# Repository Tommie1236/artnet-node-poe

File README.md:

# Art-Net Node PoE — v2

A compact, fully SMD Art-Net node with Power over Ethernet (PoE) support and two bidirectional DMX512 ports.

---

## Table of Contents

- [Overview](#overview)
- [Features](#features)
- [What is Art-Net?](#what-is-art-net)
- [What is DMX512?](#what-is-dmx512)
- [Hardware](#hardware)
  - [v1 vs v2](#v1-vs-v2)
  - [Board Design](#board-design)
  - [Power](#power)
  - [DMX Ports](#dmx-ports)
- [Getting Started](#getting-started)
  - [Powering the Node](#powering-the-node)
  - [Connecting DMX Devices](#connecting-dmx-devices)
  - [Network Configuration](#network-configuration)
- [Usage](#usage)
- [Planned Features](#planned-features)
- [Contributing](#contributing)
- [License](#license)

---

## Overview

This project is the second generation of a DIY Art-Net node — a device that bridges an Ethernet network running the [Art-Net protocol](https://art-net.org.uk/) to standard DMX512 lighting fixtures and controllers.

The v1 node ([pico-art-net-node](https://github.com/Tommie1236/pico-art-net-node)) was built around a **Raspberry Pi Pico** with separate breakout modules: a WIZnet W5500 Ethernet module, an isolated RS-485 transceiver board, and an SSD1306 OLED display. While that approach worked well for prototyping, it produced a larger assembly with many inter-board connections.

The v2 design integrates everything onto a single PCB using **fully surface-mount components** — no separate Pico module, no separate W5500 module. The result is a much more compact and reliable board. Three power inputs are supported (USB, DC jack, and PoE) with automatic hardware priority so PoE is only used when nothing else is connected. v2 also expands from one DMX port to **two independent bidirectional DMX512 ports** with XLR3 connectors, and uses an EtherCon-compatible connector for a robust Ethernet connection.

---

## Features

| Feature | v1 ([pico-art-net-node](https://github.com/Tommie1236/pico-art-net-node)) | v2 (this project) |
|---|---|---|
| PCB design | THT breakout modules (Pico, W5500, RS-485 board) | Fully SMD, single PCB |
| Microcontroller | Raspberry Pi Pico (RP2040 module) | Integrated SMD MCU |
| Ethernet | WIZnet W5500 breakout module | Integrated SMD Ethernet |
| DMX ports | 1 (output) | 2 (Port A & Port B) |
| DMX direction | Output only | Input **and** Output per port |
| Display | SSD1306 OLED | — |
| Power source | External supply only | USB, DC jack, or PoE (priority: USB > DC > PoE) |
| RDM support | No | Planned |

- **Fully SMD layout** — no bulky THT breakout modules; compact, clean, and reliable.
- **Three power inputs with automatic priority** — USB (highest), DC barrel jack, or PoE (lowest). The node automatically uses the highest-priority source available, so plugging in USB or DC disables PoE, saving switch capacity and reducing cable losses.
- **EtherCon connector** — the RJ45 Ethernet port uses an EtherCon-compatible connector/housing for a robust, locking connection in live environments.
- **Two DMX512 ports** — both Port A and Port B support DMX **output** (Art-Net → DMX) and DMX **input** (DMX → Art-Net).
- **Standard Art-Net protocol** — compatible with any Art-Net controller or software (e.g., MA Lighting, QLC+, MadMapper, sACN bridges, etc.).
- **Future RDM support** — the hardware is designed with RDM in mind for a future firmware update.

---

## What is Art-Net?

[Art-Net](https://art-net.org.uk/) is a royalty-free protocol developed by Artistic Licence that allows DMX512 data to be transmitted over standard Ethernet (UDP/IP) networks. It is widely used in professional and hobbyist stage lighting installations to send lighting control data over long distances, through network switches, and to multiple nodes simultaneously.

An Art-Net **node** acts as the bridge between the Ethernet network and physical DMX cables, converting incoming Art-Net packets into DMX512 signals (output mode) and/or reading DMX512 signals and forwarding them as Art-Net packets to the network (input mode).

---

## What is DMX512?

DMX512 (Digital Multiplex 512) is a serial communication standard used to control stage lighting, dimmers, LEDs, fog machines, and many other effects devices. A single DMX universe carries up to 512 channels of 8-bit data at a refresh rate typically around 44 Hz. Devices on the DMX bus are daisy-chained through XLR connectors — 3-pin (XLR3) or 5-pin (XLR5); both carry the same signal on pins 1–3.

---

## Hardware

### v1 vs v2

The original [v1 node (pico-art-net-node)](https://github.com/Tommie1236/pico-art-net-node) used a **Raspberry Pi Pico** (RP2040) as the microcontroller, paired with a WIZnet W5500 Ethernet breakout module, a separate isolated RS-485 transceiver board for DMX, and an SSD1306 OLED display for status info. All components were connected by wires and headers, which was great for iteration but produced a relatively bulky assembly.

v2 replaces this approach with a single, compact PCB:

- The RP2040 (or equivalent MCU) and Ethernet controller are placed as bare SMD components directly on the PCB, eliminating the stackable module approach.
- RS-485 transceivers and isolation are integrated on-board for both DMX ports.
- The PoE power extraction and regulation circuitry is integrated, alongside a DC barrel jack and USB port, with hardware priority logic (USB > DC > PoE).

### Board Design

- Single compact PCB with all components surface-mounted.
- Integrated Ethernet PHY and microcontroller section.
- Isolated RS-485 transceivers for each DMX port.
- PoE power extraction circuitry with USB and DC jack alternatives.
- Direction control logic for bidirectional DMX operation.
- EtherCon-compatible RJ45 connector/housing for a locking, strain-relieved Ethernet connection.

### Power

The node supports three power inputs with automatic hardware priority:

| Priority | Source | Notes |
|---|---|---|
| 1 (highest) | **USB** | Powers the node from any USB port or charger |
| 2 | **DC barrel jack** | Conventional external DC supply |
| 3 (lowest) | **Power over Ethernet (PoE)** | Power delivered over the Ethernet cable |

When a higher-priority source is connected, PoE is automatically disabled. This avoids drawing unnecessary power from the network switch and reduces losses in the UTP cable — there is no benefit in using PoE if a USB or DC supply is already plugged in.

### DMX Ports

The node provides **two independent DMX512 ports**, each with:

- A **3-pin XLR connector** (XLR3) — the most common connector used in practice for DMX512 equipment.
- An isolated RS-485 transceiver for electrical isolation from the network side.
- Software-configurable direction: **output** (receive Art-Net, drive DMX) or **input** (read DMX, send Art-Net).

Each port operates on its own Art-Net **universe**, configurable via the node's settings.

---

## Getting Started

### Powering the Node

The node automatically uses the highest-priority power source available.

**Option A — USB (highest priority):**

1. Connect a USB cable to the USB port on the node.
2. The node powers up immediately; DC and PoE are bypassed.

**Option B — DC barrel jack:**

1. Connect a suitable DC power supply to the barrel jack.
2. If no USB source is present, the node will run from DC; PoE is bypassed.

**Option C — PoE (lowest priority):**

1. Connect the node to a PoE-capable switch port or injector using a Cat5e/Cat6 Ethernet cable terminated in a standard RJ45 or EtherCon connector.
2. PoE is used only when neither USB nor DC is connected.

### Connecting DMX Devices

- **Output mode (Art-Net → DMX):** Connect Port A or Port B to the DMX input of a lighting fixture, dimmer rack, or the first device in a DMX chain.
- **Input mode (DMX → Art-Net):** Connect a DMX controller's DMX output to Port A or Port B to forward its signal onto the Art-Net network.

Use a standard **3-pin XLR (XLR3) cable** to connect DMX devices. If your fixture uses a 5-pin XLR connector, a passive XLR5 ↔ XLR3 adapter can be used (pins 1, 2, and 3 carry the DMX signal identically on both connector types).

Always **terminate** the end of a DMX chain with a 120 Ω terminator plug.

### Network Configuration

By default the node will attempt to obtain an IP address via DHCP. If no DHCP server is available it will fall back to a static IP (see firmware documentation for default address).

Configuration options (universe assignments, port directions, IP settings) are accessible via:

- A web-based configuration interface served by the node itself.
- Art-Net ArtAddress and ArtPoll packets from a compatible controller.

---

## Usage

1. Power the node via USB, DC jack, or PoE (whichever is available; highest priority wins).
2. Connect the node to your Ethernet network.
3. Open your Art-Net controller software and discover or manually add the node.
4. Assign Art-Net universes to Port A and Port B.
5. Connect your DMX fixtures or controllers to the XLR ports.
6. Start sending or receiving DMX data.

---

## Planned Features

- **RDM (Remote Device Management)** — The hardware already supports the bidirectional RS-485 communication required for RDM. A future firmware update will add full RDM support, allowing the node to discover and configure RDM-capable fixtures directly from Art-Net RDM controllers.
- Web UI improvements for easier configuration.
- sACN (E1.31) support alongside Art-Net.

---

## Contributing

Contributions are welcome! See [CONTRIBUTING.md](CONTRIBUTING.md) for guidelines.

---

## License

This project is licensed under the [MIT License](LICENSE).

Copyright © 2026 Timoo

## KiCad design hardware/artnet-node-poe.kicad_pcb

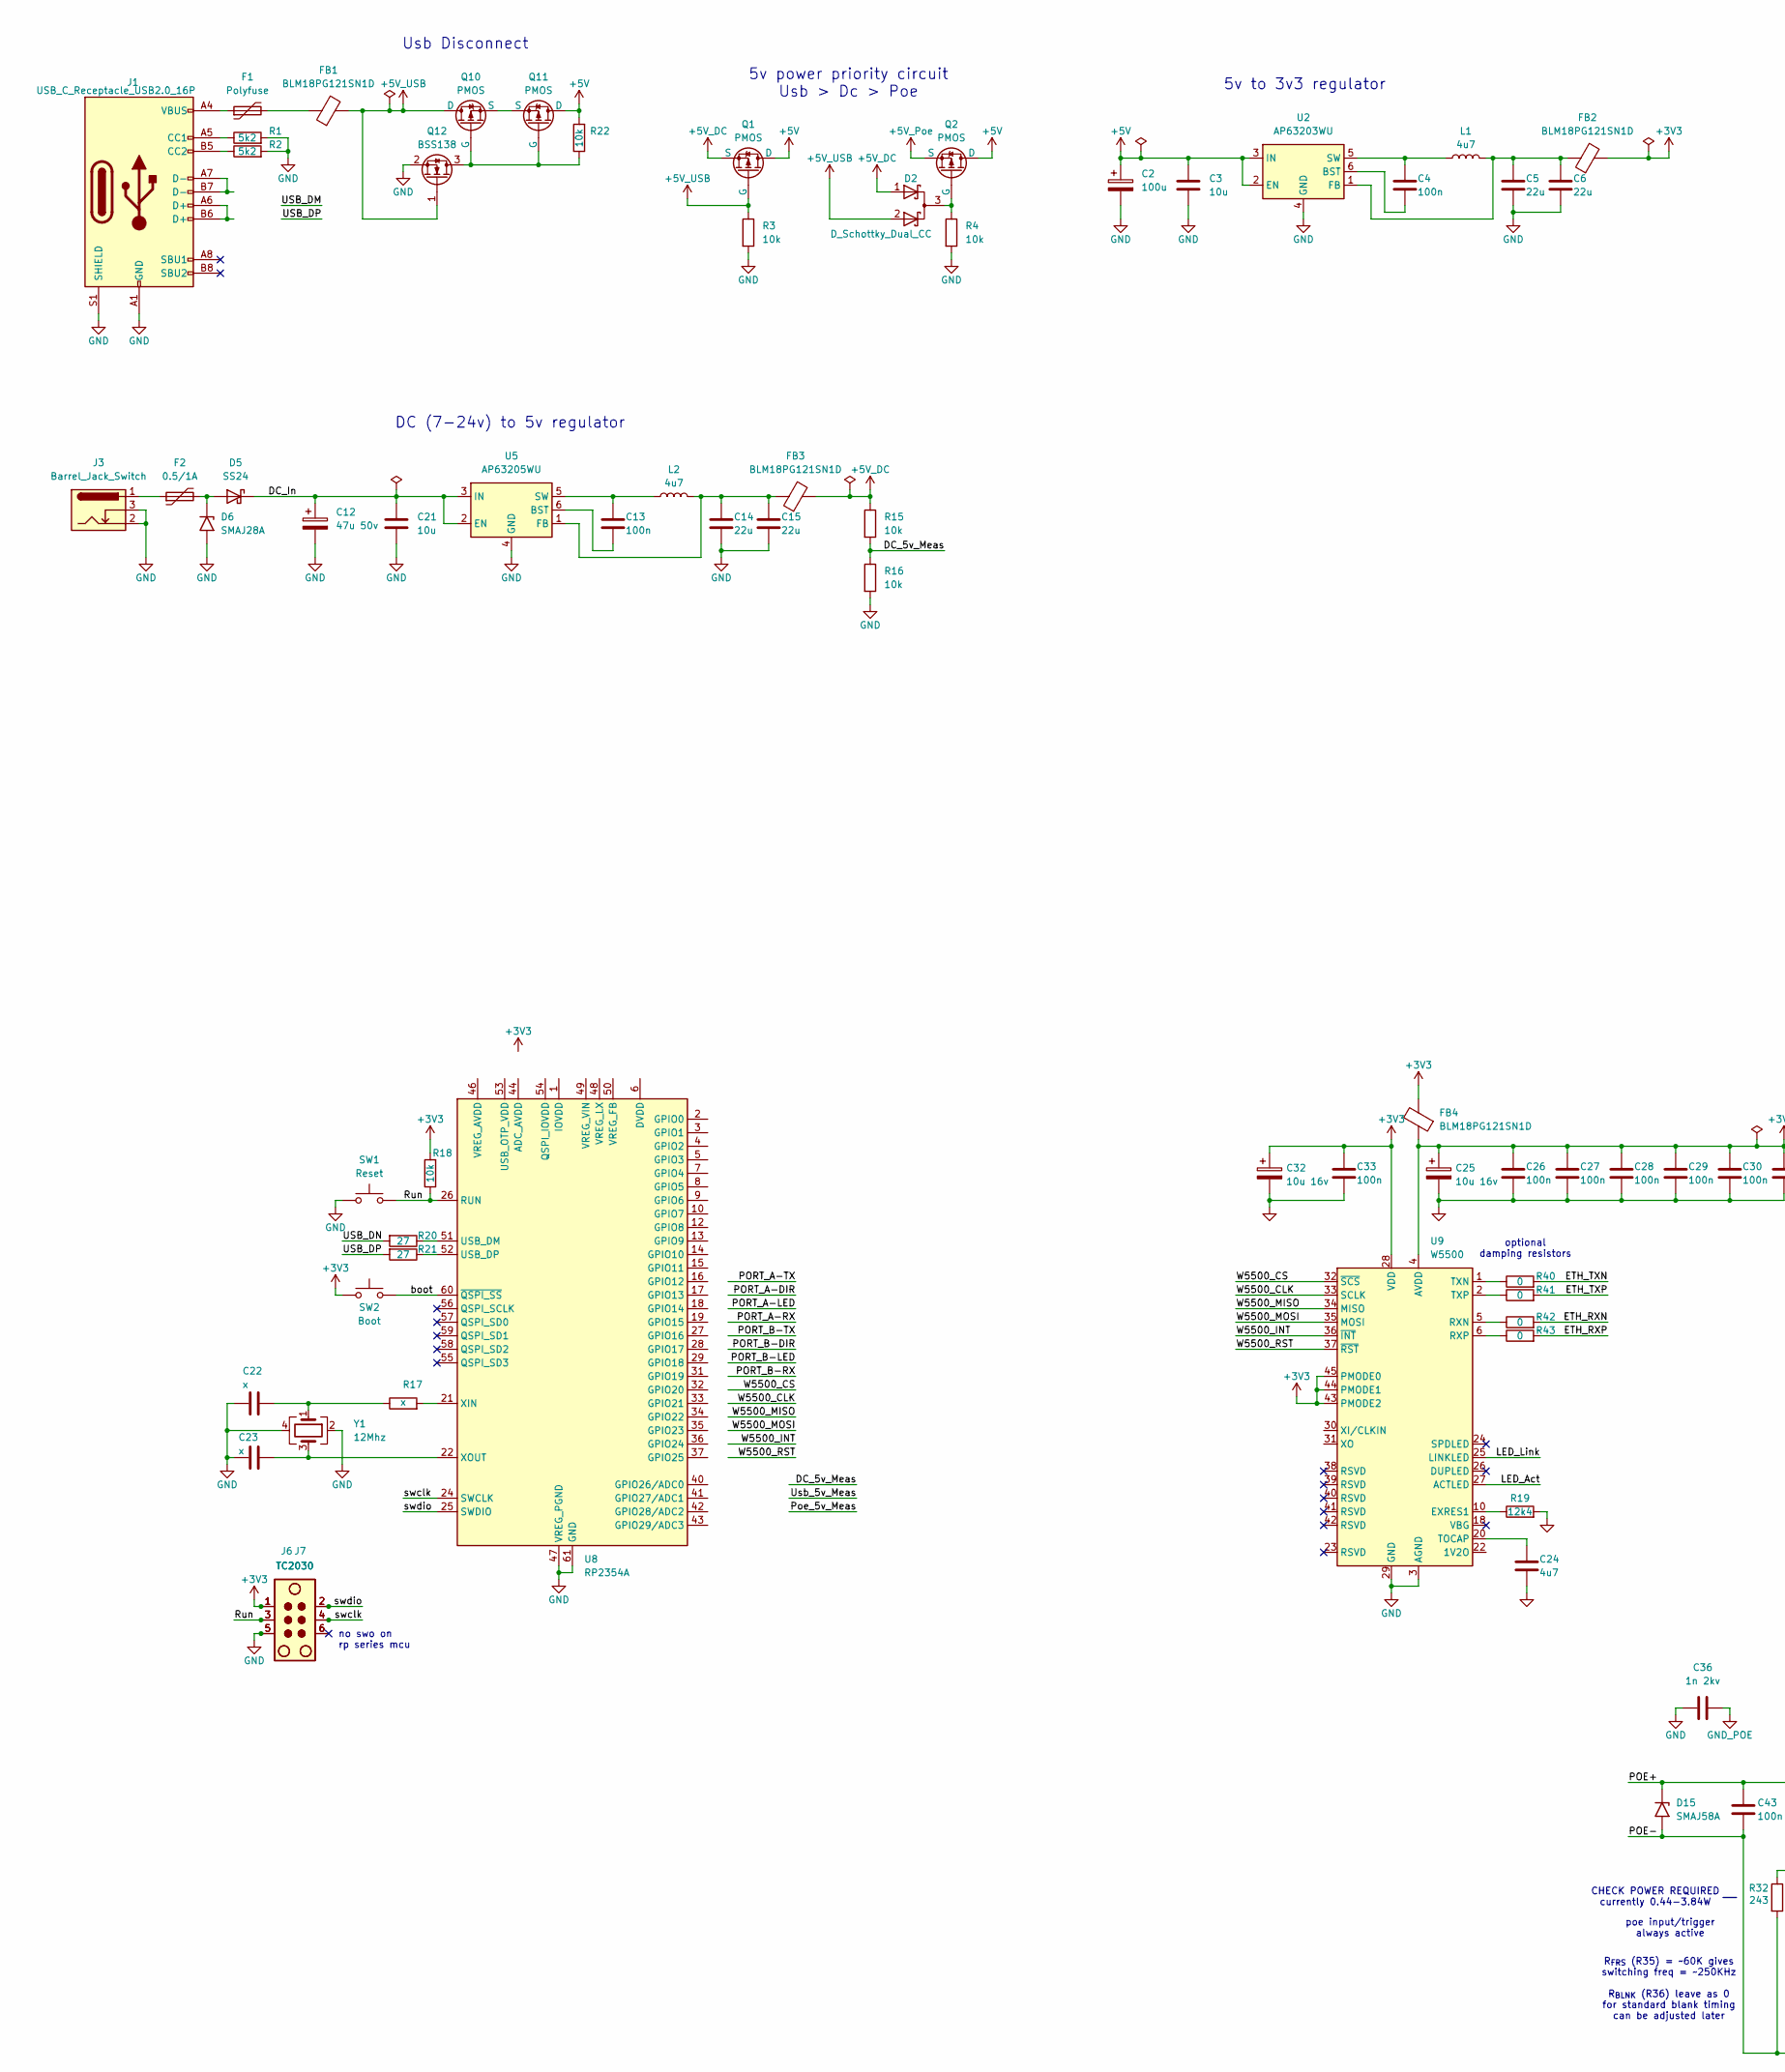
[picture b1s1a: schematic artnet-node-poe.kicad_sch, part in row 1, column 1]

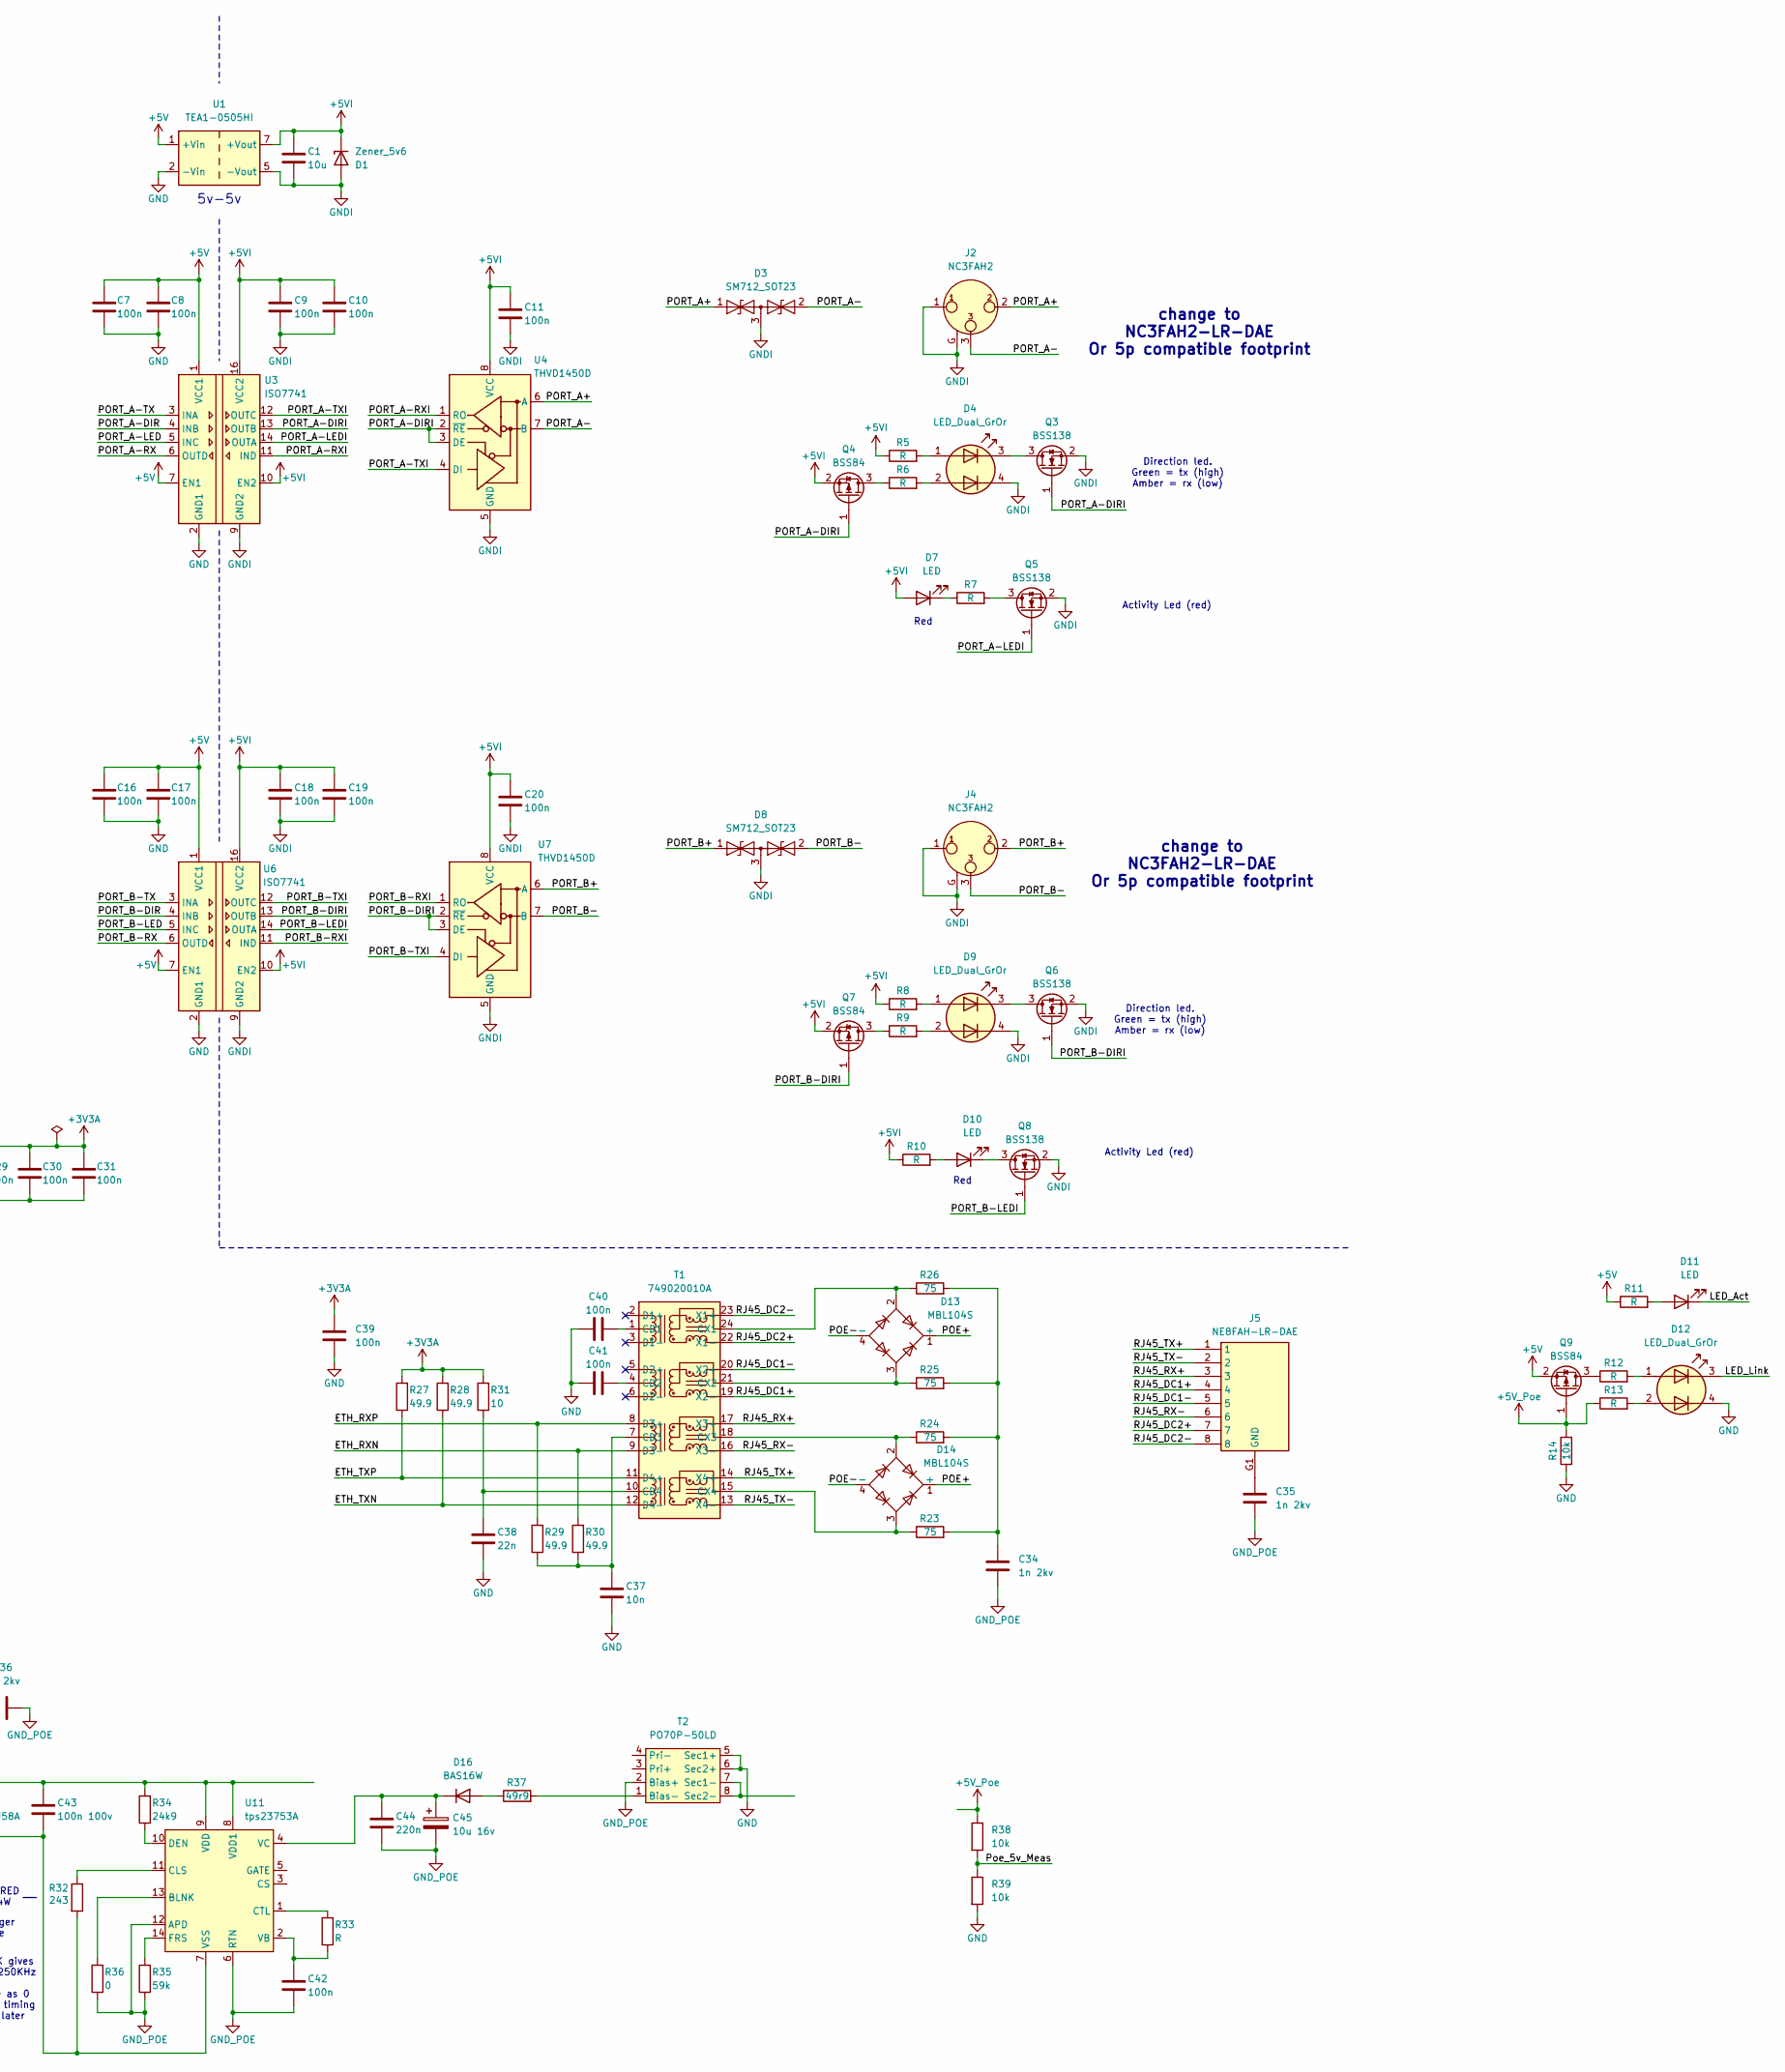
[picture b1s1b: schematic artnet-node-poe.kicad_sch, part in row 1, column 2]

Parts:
C1, C3, C21: 10u; C_0805_2012Metric
C2: 100u
C4, C7, C8, C9, C10, C11, C13, C16, C17, C18, C19, C20, C26, C27, C28, C29, C30, C31, C33, C39, C40, C41, C42: 100n; C_0603_1608Metric
C5, C6, C14, C15: 22u; C_0805_2012Metric
C12: 47u 50v
C22, C23: x; C_0603_1608Metric
C24: 4u7; C_0603_1608Metric
C25, C32, C45: 10u 16v
C34, C35, C36: 1n 2kv; C_1812_4532Metric; Mouser Part Number 80-C1812C102KGR
C37: 10n; C_0603_1608Metric
C38: 22n; C_0603_1608Metric
C43: 100n 100v
C44: 220n
D1: Zener_5v6; D_SOD-323; Mouser Part Number 863-MM3Z5V6ST1G
D2: D_Schottky_Dual_CC; SOT-23-3; Mouser Part Number 241-BAT54A_R1_00001
D3, D8: SM712_SOT23; SOT-23; Mouser Part Number 576-SM712-02HTG
D4, D9, D12: LED_Dual_GrOr; LED_LiteOn_LTST-C295K_1.6x0.8mm; Mouser Part Number 604-APHB1608CGKSEKC
D5: SS24; D_SMA; Mouser Part Number 512-SS24FL
D6: SMAJ28A; D_SMA; Mouser Part Number 621-SMAJ28A-13-F
D7, D10, D11: LED; LED_0603_1608Metric; Mouser Part Number 859-LTST-C190KRKT
D13, D14: MBL104S; Diode_Bridge_Vishay_MBLS; Mouser Part Number 621-MB10S-13
D15: SMAJ58A; D_SMA; Mouser Part Number 621-SMAJ58A-13-F
D16: BAS16W; D_SOD-323_HandSoldering; Mouser Part Number 863-BAS16HT3G
F1: Polyfuse; Fuse_0603_1608Metric; Mouser Part Number 504-PTSLR06038V050
F2: 0.5/1A; Fuse_0603_1608Metric; Mouser Part Number 504-PTSLR06038V050
FB1, FB2, FB3, FB4: BLM18PG121SN1D; L_0603_1608Metric; Mouser Part Number 81-BLM18PG121SN1D
J1: USB_C_Receptacle_USB2.0_16P; USB_C_Receptacle_GCT_USB4105-xx-A_16P_TopMnt_Horizontal; Mouser Part Number 640-USB4930-00-A
J2, J4: NC3FAH2; Jack_XLR_Neutrik_NC3FAH2_Horizontal; Mouser Part Number 568-NC3FAH2-LR-DAE
J3: Barrel_Jack_Switch; BarrelJack_Horizontal
J5: NE8FAH-LR-DAE; NE8FAHLRDAE; Mouser Part Number 568-NE8FAH-LR-DAE
J6, J7: TC2030; Tag-Connect_TC2030-IDC-FP_2x03_P1.27mm_Vertical
L1, L2: 4u7; SPM4012-LR; Mouser Part Number 810-SPM4012T4R7MLR
Q1, Q2, Q10, Q11: PMOS; Mouser Part Number 621-DMG2305UX-7
Q3, Q5, Q6, Q8, Q12: BSS138; SOT-23
Q4, Q7, Q9: BSS84; SOT-23
R1, R2: 5k2; R_0603_1608Metric
R3, R4, R14, R15, R16, R18, R22, R38, R39: 10k; R_0603_1608Metric
R5, R6, R7, R8, R9, R10, R11, R12, R13, R33: R; R_0603_1608Metric
R17: x; R_0603_1608Metric
R19: 12k4; R_0603_1608Metric
R20, R21: 27; R_0603_1608Metric
R23, R24, R25, R26: 75; R_0805_2012Metric; Mouser Part Number 603-RC0805FR-0775RL
R27, R28, R29, R30: 49.9; R_0603_1608Metric
R31: 10; R_0603_1608Metric
R32: 243; R_0603_1608Metric
R34: 24k9; R_0603_1608Metric
R35: 59k; R_0603_1608Metric
R36, R40, R41, R42, R43: 0; R_0603_1608Metric
R37: 49r9; R_0603_1608Metric; Mouser Part Number 603-RC0805FR-0775RL
SW1: Reset
SW2: Boot
T1: 749020010A; Transformer_Ethernet_Bourns_PT61020EL; Mouser Part Number 710-749020010A
T2: PO70P-50LD; POE70P-50LD
U1: TEA1-0505HI; Converter_DCDC_TRACO_TEA1-xxxxHI_THT; Mouser Part Number 495-TEA1-0505HI
U2: AP63203WU; TSOT-23-6; Mouser Part Number 621-AP63203WU-7
U3, U6: ISO7741; SOIC-16W_7.5x10.3mm_P1.27mm; Mouser Part Number 595-ISO7741EDWRQ1
U4, U7: THVD1450D; SOIC-8_3.9x4.9mm_P1.27mm; Mouser Part Number 595-THVD1450DRBR
U5: AP63205WU; TSOT-23-6; Mouser Part Number 621-AP63205WU-7
U8: RP2354A; QFN-60-1EP_7x7mm_P0.4mm_EP3.4x3.4mm; Mouser Part Number 358-SC151113
U9: W5500; LQFP-48_7x7mm_P0.5mm; Mouser Part Number 950-W5500
U11: tps23753A; TSSOP-14_4.4x5mm_P0.65mm
Y1: 12Mhz

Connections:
+3V3: C32.1, C33.1, FB2.2, FB4.2, J6.1, J7.1, R18.2, SW2.1, U9.28 (VDD), U9.43 (PMODE2), U9.44 (PMODE1), U9.45 (PMODE0)
+3V3A: C25.1, C26.1, C27.1, C28.1, C29.1, C30.1, C31.1, C39.1, FB4.1, R27.2, R28.2, R31.2, U9.4 (AVDD), U9.8 (AVDD), U9.11 (AVDD), U9.15 (AVDD), U9.17 (AVDD), U9.21 (AVDD)
+5V: C2.1, C3.1, C7.1, C8.1, C16.1, C17.1, Q1.2 (D), Q2.2 (D), Q9.2 (S), Q11.2 (D), R11.1, R22.2, U1.1 (+Vin), U2.2 (EN), U2.3 (IN), U3.1 (VCC1), U3.7 (EN1), U6.1 (VCC1), U6.7 (EN1)
+5VI: C1.1, C9.1, C10.1, C11.1, C18.1, C19.1, C20.1, D1.1 (K), D7.2 (A), Q4.2 (S), Q7.2 (S), R5.1, R8.1, R10.1, U1.7 (+Vout), U3.10 (EN2), U3.16 (VCC2), U4.8 (VCC), U6.10 (EN2), U6.16 (VCC2), U7.8 (VCC)
+5V_DC: D2.1 (A), FB3.2, Q1.3 (S), R15.1
+5V_Poe: Q2.3 (S), Q9.1 (G), R13.1, R14.2, R38.1
+5V_USB: D2.2 (A), FB1.2, Q1.1 (G), Q10.2 (D), Q12.1 (G), R3.1
/DC_5v_Meas: R15.2, R16.1
/DC_In: C12.1, C21.1, D5.1 (K), U5.2 (EN), U5.3 (IN)
/ETH_RXN: R30.2, R42.2, T1.9 (D3-)
/ETH_RXP: R29.2, R43.2, T1.8 (D3+)
/ETH_TXN: R28.1, R40.2, T1.12 (D4-)
/ETH_TXP: R27.1, R41.2, T1.11 (D4+)
/LED_Act: D11.1 (K), U9.27 (ACTLED)
/LED_Link: D12.3 (K1), U9.25 (LINKLED)
/POE+: C43.1, D13.1 (+), D14.1 (+), D15.1 (A1), R34.2, U11.8 (VDD1), U11.9 (VDD)
/POE-: C43.2, D13.4 (-), D14.4 (-), D15.2 (A2), R32.2, U11.7 (VSS)
/PORT_A+: D3.1 (A1), J2.2, U4.6 (A)
/PORT_A-: D3.2 (A2), J2.3, U4.7 (B)
/PORT_A-DIR: U3.4 (INB)
/PORT_A-DIRI: Q3.1 (G), Q4.1 (G), U3.13 (OUTB), U4.2 (~RE), U4.3 (DE)
/PORT_A-LED: U3.5 (INC)
/PORT_A-LEDI: Q5.1 (G), U3.14 (OUTA)
/PORT_A-RX: U3.6 (OUTD)
/PORT_A-RXI: U3.11 (IND), U4.1 (RO)
/PORT_A-TX: U3.3 (INA)
/PORT_A-TXI: U3.12 (OUTC), U4.4 (DI)
/PORT_B+: D8.1 (A1), J4.2, U7.6 (A)
/PORT_B-: D8.2 (A2), J4.3, U7.7 (B)
/PORT_B-DIR: U6.4 (INB)
/PORT_B-DIRI: Q6.1 (G), Q7.1 (G), U6.13 (OUTB), U7.2 (~RE), U7.3 (DE)
/PORT_B-LED: U6.5 (INC)
/PORT_B-LEDI: Q8.1 (G), U6.14 (OUTA)
/PORT_B-RX: U6.6 (OUTD)
/PORT_B-RXI: U6.11 (IND), U7.1 (RO)
/PORT_B-TX: U6.3 (INA)
/PORT_B-TXI: U6.12 (OUTC), U7.4 (DI)
/Poe_5v_Meas: R38.2, R39.1
/RJ45_DC1+: J5.4, T1.19 (X2-)
/RJ45_DC1-: J5.5, T1.20 (X2+)
/RJ45_DC2+: J5.7, T1.22 (X1-)
/RJ45_DC2-: J5.8, T1.23 (X1+)
/RJ45_RX+: J5.3, T1.17 (X3+)
/RJ45_RX-: J5.6, T1.16 (X3-)
/RJ45_TX+: J5.1, T1.14 (X4+)
/RJ45_TX-: J5.2, T1.13 (X4-)
/Run: J6.3, J7.3, R18.1, SW1.2, U8.26 (RUN)
/USB_DN: R20.2
/USB_DP: R21.2
/W5500_CLK: U9.33 (SCLK)
/W5500_CS: U9.32 (~SCS)
/W5500_INT: U9.36 (~INT)
/W5500_MISO: U9.34 (MISO)
/W5500_MOSI: U9.35 (MOSI)
/W5500_RST: U9.37 (~RST)
/boot: SW2.2, U8.60 (~QSPI_SS)
/swclk: J6.4, J7.4, U8.24 (SWCLK)
/swdio: J6.2, J7.2, U8.25 (SWDIO)
GND: C2.2, C3.2, C5.2, C6.2, C7.2, C8.2, C12.2, C14.2, C15.2, C16.2, C17.2, C21.2, C22.1, C23.1, C24.2, C25.2, C26.2, C27.2, C28.2, C29.2, C30.2, C31.2, C32.2, C33.2, C36.1, C37.2, C38.2, C39.2, C40.1, C41.1, D6.2 (A2), D12.4 (K2), J1.A1 (GND), J1.A12 (GND), J1.B1 (GND), J1.B12 (GND), J1.S1 (SHIELD), J3.2, J3.3, J6.5, J7.5, Q12.2 (S), R1.2, R2.2, R3.2, R4.2, R14.1, R16.2, R19.2, R39.2, SW1.1, T2.5 (Sec1+), T2.6 (Sec2+), U1.2 (-Vin), U2.4 (GND), U3.2 (GND1), U3.8 (GND1), U5.4 (GND), U6.2 (GND1), U6.8 (GND1), U8.47 (VREG_PGND), U8.61 (GND), U9.3 (AGND), U9.9 (AGND), U9.14 (AGND), U9.16 (AGND), U9.19 (AGND), U9.29 (GND), U9.48 (AGND), Y1.2 (G), Y1.4 (G)
GNDI: C1.2, C9.2, C10.2, C11.2, C18.2, C19.2, C20.2, D1.2 (A), D3.3 (common), D4.4 (K2), D8.3 (common), D9.4 (K2), J2.1, J2.G, J4.1, J4.G, Q3.2 (S), Q5.2 (S), Q6.2 (S), Q8.2 (S), U1.5 (-Vout), U3.9 (GND2), U3.15 (GND2), U4.5 (GND), U6.9 (GND2), U6.15 (GND2), U7.5 (GND)
GND_POE: C34.2, C35.2, C36.2, C42.2, C44.2, C45.2, R35.1, R36.1, T2.2 (Bias+), U11.6 (RTN), U11.12 (APD)
unnamed: C22.2, R17.1, Y1.1
unnamed: C34.1, R23.2, R24.2, R25.2, R26.2
unnamed: D2.3 (K), Q2.1 (G), R4.1
unnamed: D4.1 (A1), R5.2
unnamed: D4.2 (A2), R6.2
unnamed: D4.3 (K1), Q3.3 (D)
unnamed: D5.2 (A), D6.1 (A1), F2.2
unnamed: D7.1 (K), R7.1
unnamed: D9.1 (A1), R8.2
unnamed: D9.2 (A2), R9.2
unnamed: D9.3 (K1), Q6.3 (D)
unnamed: D10.2 (A), R10.2
unnamed: D10.1 (K), Q8.3 (D)
unnamed: D11.2 (A), R11.2
unnamed: D12.1 (A1), R12.2
unnamed: D12.2 (A2), R13.2
unnamed: D16.2 (A), R37.1
unnamed: C44.1, C45.1, D16.1 (K), U11.4 (VC)
unnamed: F1.1, J1.A4 (VBUS), J1.A9 (VBUS), J1.B4 (VBUS), J1.B9 (VBUS)
unnamed: F1.2, FB1.1
unnamed: F2.1, J3.1
unnamed: J1.A5 (CC1), R1.1
unnamed: J1.B5 (CC2), R2.1
unnamed: J1.A6 (D+), J1.B6 (D+)
unnamed: J1.A7 (D-), J1.B7 (D-)
unnamed: C35.1, J5.G1 (GND)
unnamed: Q4.3 (D), R6.1
unnamed: Q5.3 (D), R7.2
unnamed: Q7.3 (D), R9.1
unnamed: Q9.3 (D), R12.1
unnamed: Q10.1 (G), Q11.1 (G), Q12.3 (D), R22.1
unnamed: Q10.3 (S), Q11.3 (S)
unnamed: C40.2, T1.1 (CD1)
unnamed: C41.2, T1.4 (CD2)
unnamed: C37.1, R29.1, R30.1, T1.7 (CD3)
unnamed: C38.1, R31.1, T1.10 (CD4)
unnamed: D13.2, R26.1, T1.24 (CX1)
unnamed: D13.3, R25.1, T1.21 (CX2)
unnamed: D14.2, R24.1, T1.18 (CX3)
unnamed: D14.3, R23.1, T1.15 (CX4)
unnamed: R37.2, T2.1 (Bias-)
unnamed: T2.7 (Sec1-), T2.8 (Sec2-)
unnamed: C4.2, U2.6 (BST)
unnamed: C5.1, C6.1, FB2.1, L1.2, U2.1 (FB)
unnamed: C4.1, L1.1, U2.5 (SW)
unnamed: C13.2, U5.6 (BST)
unnamed: C14.1, C15.1, FB3.1, L2.2, U5.1 (FB)
unnamed: C13.1, L2.1, U5.5 (SW)
unnamed: U8.6 (DVDD), U8.23 (DVDD), U8.39 (DVDD)
unnamed: U8.1 (IOVDD), U8.11 (IOVDD), U8.20 (IOVDD), U8.30 (IOVDD), U8.38 (IOVDD), U8.45 (IOVDD)
unnamed: R20.1, U8.51 (USB_DM)
unnamed: R21.1, U8.52 (USB_DP)
unnamed: R17.2, U8.21 (XIN)
unnamed: C23.2, U8.22 (XOUT), Y1.3
unnamed: R19.1, U9.10 (EXRES1)
unnamed: R42.1, U9.5 (RXN)
unnamed: R43.1, U9.6 (RXP)
unnamed: C24.1, U9.20 (TOCAP)
unnamed: R40.1, U9.1 (TXN)
unnamed: R41.1, U9.2 (TXP)
unnamed: R36.2, U11.13 (BLNK)
unnamed: R32.1, U11.11 (CLS)
unnamed: R33.2, U11.1 (CTL)
unnamed: R34.1, U11.10 (DEN)
unnamed: R35.2, U11.14 (FRS)
unnamed: C42.1, R33.1, U11.2 (VB)

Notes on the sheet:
Direction led. Green = tx (high) Amber = rx (low)
Usb Disconnect
5v to 3v3 regulator
no swo on rp series mcu
Activity Led (red)
Red
R_{FRS} (R35) = ~60K gives switching freq = ~250KHz R_{BLNK} (R36) leave as 0 for standard blank timing can be adjusted later
5v power priority circuit Usb > Dc > Poe
CHECK POWER REQUIRED currently 0.44-3.84W
5v-5v
change to NC3FAH2-LR-DAE Or 5p compatible footprint
optional damping resistors
DC (7-24v) to 5v regulator
poe input/trigger always active

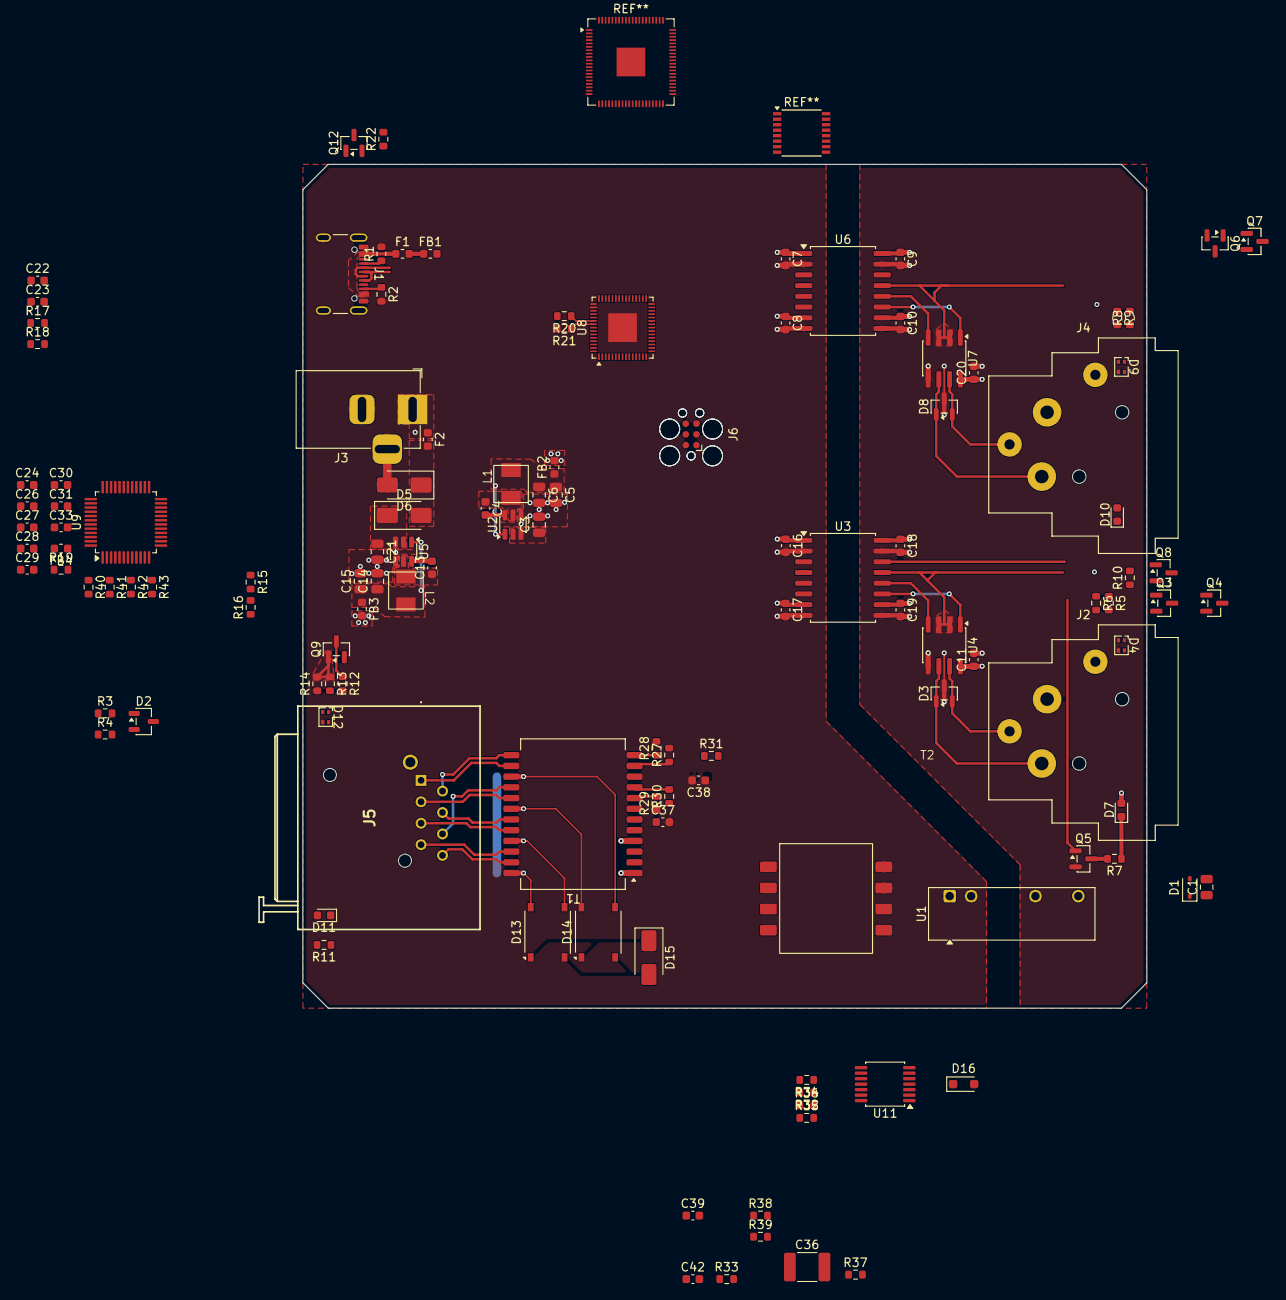
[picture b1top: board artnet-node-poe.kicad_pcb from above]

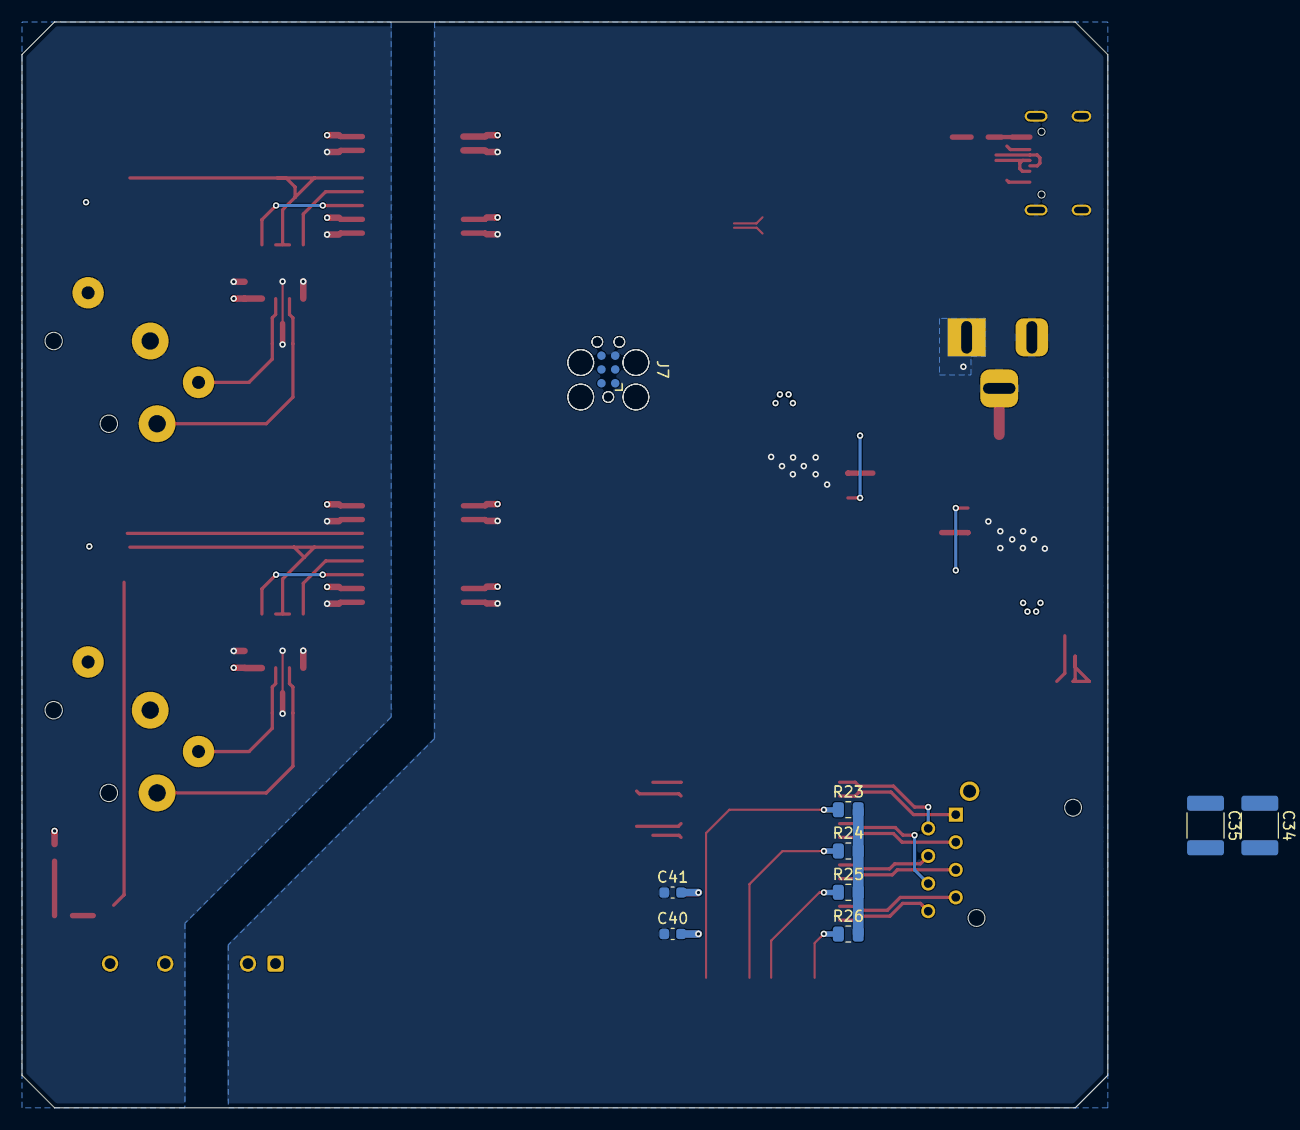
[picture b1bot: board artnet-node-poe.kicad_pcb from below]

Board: 4 copper layers, 100.0 x 100.0 mm, 132 parts (9 on the bottom side), 109 nets.

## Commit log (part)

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2026-04-06 Initial plan
2026-04-06 Add comprehensive README and CONTRIBUTING docs with accurate v1 reference
    Agent-Logs-Url: https://github.com/Tommie1236/artnet-node-poe/sessions/d4218e37-2f03-4824-9daf-627cbdc93d38
2026-04-06 Update README: XLR3 connectors, three power inputs with priority, EtherCon Ethernet
    Agent-Logs-Url: https://github.com/Tommie1236/artnet-node-poe/sessions/483e5434-5294-4203-b534-daf931a4d84f
